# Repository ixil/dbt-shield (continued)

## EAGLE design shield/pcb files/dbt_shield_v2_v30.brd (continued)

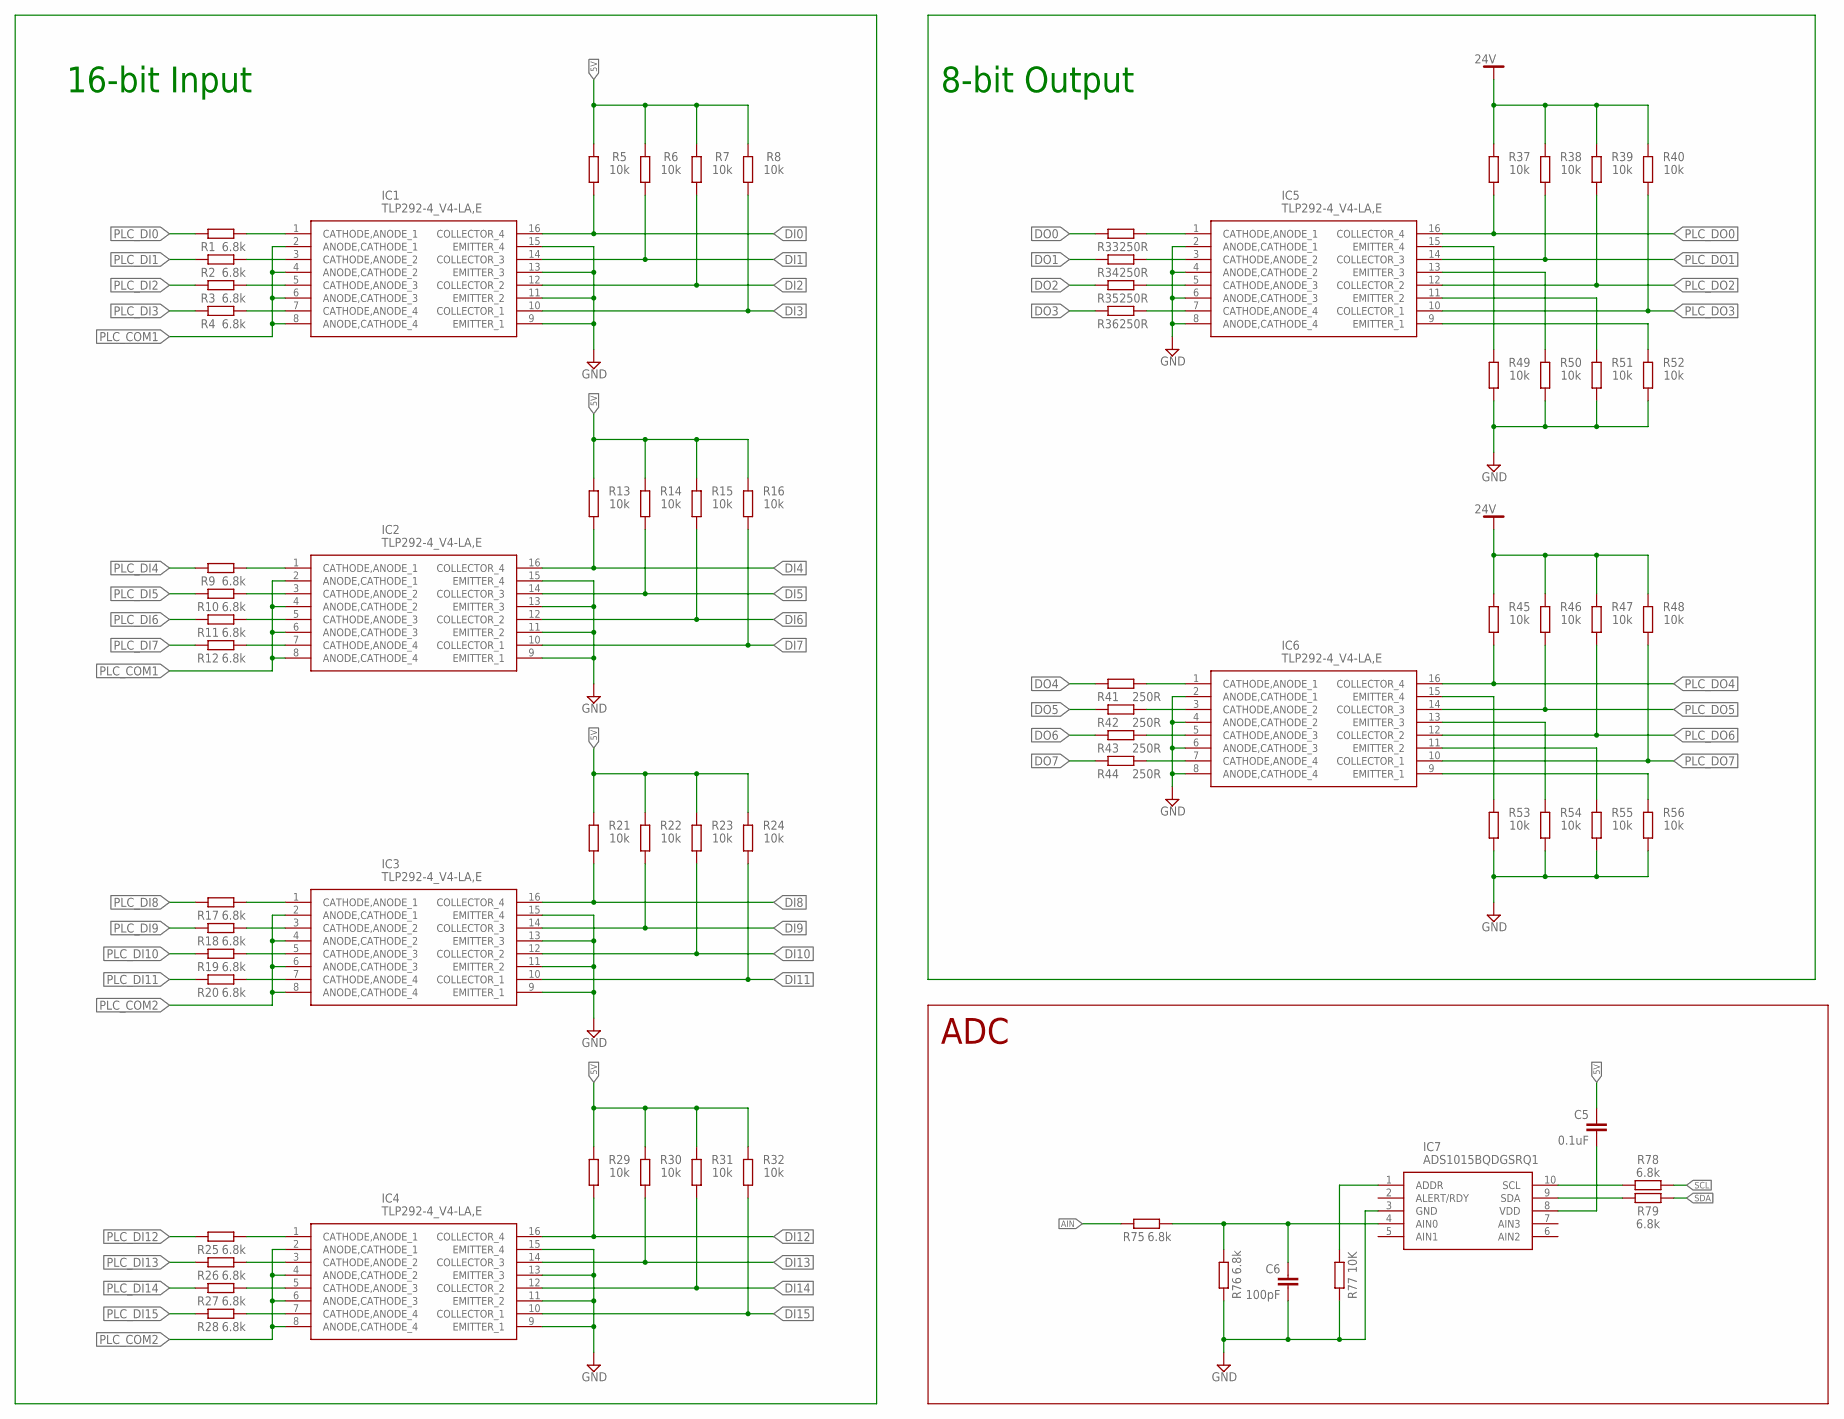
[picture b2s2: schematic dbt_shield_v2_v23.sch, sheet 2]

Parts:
C5: 0.1uF; CAPC3216X135
C6: 100pF; CAPC3216X135
IC1, IC2, IC3, IC4, IC5, IC6: TLP292-4_V4-LA,E; SOIC127P700X230-16N
IC7: ADS1015BQDGSRQ1; SOP50P490X110-10N
R1, R2, R3, R4, R9, R10, R11, R12, R17, R18, R19, R20, R25, R26, R27, R28, R75, R76, R78, R79: 6.8k; RESC3216X70
R5, R6, R7, R8, R13, R14, R15, R16, R21, R22, R23, R24, R29, R30, R31, R32, R37, R38, R39, R40, R45, R46, R47, R48, R49, R50, R51, R52, R53, R54, R55, R56: 10k; RESC3216X70
R33, R34, R35, R36, R41, R42, R43, R44: 250R; RESC3216X70
R77: 10K; RESC3216X70

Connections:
5V: C5.1, R5.2, R6.2, R7.2, R8.2, R13.2, R14.2, R15.2, R16.2, R21.2, R22.2, R23.2, R24.2, R29.2, R30.2, R31.2, R32.2; also elsewhere on the board
24V: R37.2, R38.2, R39.2, R40.2, R45.2, R46.2, R47.2, R48.2; also elsewhere on the board
AIN: R75.1; also elsewhere on the board
DI0: IC1.16 (COLLECTOR_4), R5.1; also elsewhere on the board
DI1: IC1.14 (COLLECTOR_3), R6.1; also elsewhere on the board
DI2: IC1.12 (COLLECTOR_2), R7.1; also elsewhere on the board
DI3: IC1.10 (COLLECTOR_1), R8.1; also elsewhere on the board
DI4: IC2.16 (COLLECTOR_4), R13.1; also elsewhere on the board
DI5: IC2.14 (COLLECTOR_3), R14.1; also elsewhere on the board
DI6: IC2.12 (COLLECTOR_2), R15.1; also elsewhere on the board
DI7: IC2.10 (COLLECTOR_1), R16.1; also elsewhere on the board
DI8: IC3.16 (COLLECTOR_4), R21.1; also elsewhere on the board
DI9: IC3.14 (COLLECTOR_3), R22.1; also elsewhere on the board
DI10: IC3.12 (COLLECTOR_2), R23.1; also elsewhere on the board
DI11: IC3.10 (COLLECTOR_1), R24.1; also elsewhere on the board
DI12: IC4.16 (COLLECTOR_4), R29.1; also elsewhere on the board
DI13: IC4.14 (COLLECTOR_3), R30.1; also elsewhere on the board
DI14: IC4.12 (COLLECTOR_2), R31.1; also elsewhere on the board
DI15: IC4.10 (COLLECTOR_1), R32.1; also elsewhere on the board
DO0: R33.1; also elsewhere on the board
DO1: R34.1; also elsewhere on the board
DO2: R35.1; also elsewhere on the board
DO3: R36.1; also elsewhere on the board
DO4: R41.1; also elsewhere on the board
DO5: R42.1; also elsewhere on the board
DO6: R43.1; also elsewhere on the board
DO7: R44.1; also elsewhere on the board
GND: C6.2, IC1.9 (EMITTER_1), IC1.11 (EMITTER_2), IC1.13 (EMITTER_3), IC1.15 (EMITTER_4), IC2.9 (EMITTER_1), IC2.11 (EMITTER_2), IC2.13 (EMITTER_3), IC2.15 (EMITTER_4), IC3.9 (EMITTER_1), IC3.11 (EMITTER_2), IC3.13 (EMITTER_3), IC3.15 (EMITTER_4), IC4.9 (EMITTER_1), IC4.11 (EMITTER_2), IC4.13 (EMITTER_3), IC4.15 (EMITTER_4), IC5.2 (ANODE,CATHODE_1), IC5.4 (ANODE,CATHODE_2), IC5.6 (ANODE,CATHODE_3), IC5.8 (ANODE,CATHODE_4), IC6.2 (ANODE,CATHODE_1), IC6.4 (ANODE,CATHODE_2), IC6.6 (ANODE,CATHODE_3), IC6.8 (ANODE,CATHODE_4), IC7.3 (GND), R49.1, R50.1, R51.1, R52.1, R53.1, R54.1, R55.1, R56.1, R76.1, R77.1; also elsewhere on the board
unnamed: IC1.1 (CATHODE,ANODE_1), R1.2
unnamed: IC1.3 (CATHODE,ANODE_2), R2.2
unnamed: IC1.5 (CATHODE,ANODE_3), R3.2
unnamed: IC1.7 (CATHODE,ANODE_4), R4.2
unnamed: IC2.1 (CATHODE,ANODE_1), R9.2
unnamed: IC2.3 (CATHODE,ANODE_2), R10.2
unnamed: IC2.5 (CATHODE,ANODE_3), R11.2
unnamed: IC2.7 (CATHODE,ANODE_4), R12.2
unnamed: IC3.1 (CATHODE,ANODE_1), R17.2
unnamed: IC3.3 (CATHODE,ANODE_2), R18.2
unnamed: IC3.5 (CATHODE,ANODE_3), R19.2
unnamed: IC3.7 (CATHODE,ANODE_4), R20.2
unnamed: IC4.1 (CATHODE,ANODE_1), R25.2
unnamed: IC4.3 (CATHODE,ANODE_2), R26.2
unnamed: IC4.5 (CATHODE,ANODE_3), R27.2
unnamed: IC4.7 (CATHODE,ANODE_4), R28.2
unnamed: IC5.1 (CATHODE,ANODE_1), R33.2
unnamed: IC5.3 (CATHODE,ANODE_2), R34.2
unnamed: IC5.5 (CATHODE,ANODE_3), R35.2
unnamed: IC5.7 (CATHODE,ANODE_4), R36.2
unnamed: IC6.1 (CATHODE,ANODE_1), R41.2
unnamed: IC6.3 (CATHODE,ANODE_2), R42.2
unnamed: IC6.5 (CATHODE,ANODE_3), R43.2
unnamed: IC6.7 (CATHODE,ANODE_4), R44.2
unnamed: IC5.15 (EMITTER_4), R49.2
unnamed: IC5.13 (EMITTER_3), R50.2
unnamed: IC5.11 (EMITTER_2), R51.2
unnamed: IC5.9 (EMITTER_1), R52.2
unnamed: IC6.15 (EMITTER_4), R53.2
unnamed: IC6.13 (EMITTER_3), R54.2
unnamed: IC6.11 (EMITTER_2), R55.2
unnamed: IC6.9 (EMITTER_1), R56.2
unnamed: C6.1, IC7.4 (AIN0), R75.2, R76.2
unnamed: IC7.1 (ADDR), R77.2
unnamed: C5.2, IC7.8 (VDD)
unnamed: IC7.9 (SDA), R79.2
unnamed: IC7.10 (SCL), R78.2
PLC_COM1: IC1.2 (ANODE,CATHODE_1), IC1.4 (ANODE,CATHODE_2), IC1.6 (ANODE,CATHODE_3), IC1.8 (ANODE,CATHODE_4), IC2.2 (ANODE,CATHODE_1), IC2.4 (ANODE,CATHODE_2), IC2.6 (ANODE,CATHODE_3), IC2.8 (ANODE,CATHODE_4); also elsewhere on the board
PLC_COM2: IC3.2 (ANODE,CATHODE_1), IC3.4 (ANODE,CATHODE_2), IC3.6 (ANODE,CATHODE_3), IC3.8 (ANODE,CATHODE_4), IC4.2 (ANODE,CATHODE_1), IC4.4 (ANODE,CATHODE_2), IC4.6 (ANODE,CATHODE_3), IC4.8 (ANODE,CATHODE_4); also elsewhere on the board
PLC_DI0: R1.1; also elsewhere on the board
PLC_DI1: R2.1; also elsewhere on the board
PLC_DI2: R3.1; also elsewhere on the board
PLC_DI3: R4.1; also elsewhere on the board
PLC_DI4: R9.1; also elsewhere on the board
PLC_DI5: R10.1; also elsewhere on the board
PLC_DI6: R11.1; also elsewhere on the board
PLC_DI7: R12.1; also elsewhere on the board
PLC_DI8: R17.1; also elsewhere on the board
PLC_DI9: R18.1; also elsewhere on the board
PLC_DI10: R19.1; also elsewhere on the board
PLC_DI11: R20.1; also elsewhere on the board
PLC_DI12: R25.1; also elsewhere on the board
PLC_DI13: R26.1; also elsewhere on the board
PLC_DI14: R27.1; also elsewhere on the board
PLC_DI15: R28.1; also elsewhere on the board
PLC_DO0: IC5.16 (COLLECTOR_4), R37.1; also elsewhere on the board
PLC_DO1: IC5.14 (COLLECTOR_3), R38.1; also elsewhere on the board
PLC_DO2: IC5.12 (COLLECTOR_2), R39.1; also elsewhere on the board
PLC_DO3: IC5.10 (COLLECTOR_1), R40.1; also elsewhere on the board
PLC_DO4: IC6.16 (COLLECTOR_4), R45.1; also elsewhere on the board
PLC_DO5: IC6.14 (COLLECTOR_3), R46.1; also elsewhere on the board
PLC_DO6: IC6.12 (COLLECTOR_2), R47.1; also elsewhere on the board
PLC_DO7: IC6.10 (COLLECTOR_1), R48.1; also elsewhere on the board
SCL: R78.1; also elsewhere on the board
SDA: R79.1; also elsewhere on the board

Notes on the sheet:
16-bit Input
8-bit Output
ADC

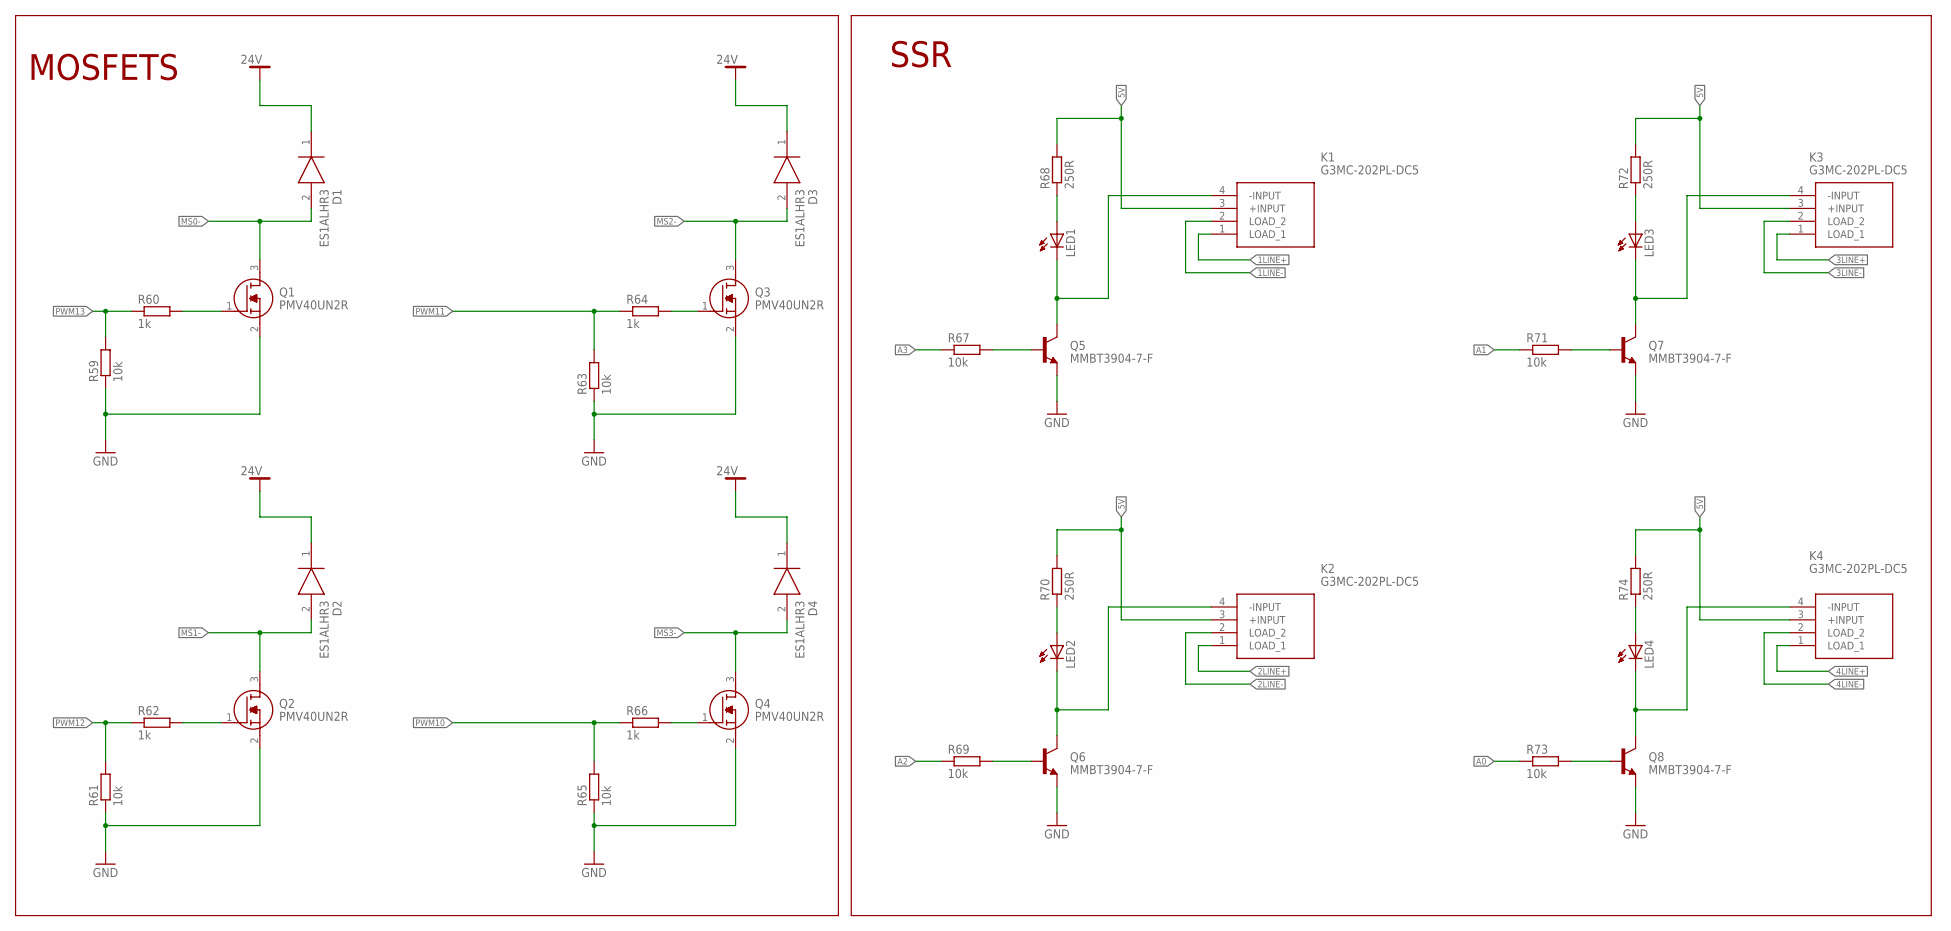
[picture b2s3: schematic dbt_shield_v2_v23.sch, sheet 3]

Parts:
D1, D2, D3, D4: ES1ALHR3; SODFL3618X143N
K1, K2, K3, K4: G3MC-202PL-DC5; G3MC202PLDC5
LED1, LED2, LED3, LED4: LEDCHIPLED_1206; CHIPLED_1206
Q1, Q2, Q3, Q4: PMV40UN2R; SOT95P230X110-3N
Q5, Q6, Q7, Q8: MMBT3904-7-F; SOT95P230X110-3N1
R59, R61, R63, R65, R67, R69, R71, R73: 10k; RESC3216X70
R60, R62, R64, R66: 1k; RESC3216X70
R68, R70, R72, R74: 250R; RESC3216X70

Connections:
1LINE+: K1.1 (LOAD_1); also elsewhere on the board
1LINE-: K1.2 (LOAD_2); also elsewhere on the board
2LINE+: K2.1 (LOAD_1); also elsewhere on the board
2LINE-: K2.2 (LOAD_2); also elsewhere on the board
3LINE+: K3.1 (LOAD_1); also elsewhere on the board
3LINE-: K3.2 (LOAD_2); also elsewhere on the board
4LINE+: K4.1 (LOAD_1); also elsewhere on the board
4LINE-: K4.2 (LOAD_2); also elsewhere on the board
5V: K1.3 (+INPUT), K2.3 (+INPUT), K3.3 (+INPUT), K4.3 (+INPUT), R68.2, R70.2, R72.2, R74.2; also elsewhere on the board
24V: D1.1 (K), D2.1 (K), D3.1 (K), D4.1 (K); also elsewhere on the board
A0: R73.1; also elsewhere on the board
A1: R71.1; also elsewhere on the board
A2: R69.1; also elsewhere on the board
A3: R67.1; also elsewhere on the board
GND: Q1.2 (S), Q2.2 (S), Q3.2 (S), Q4.2 (S), Q5.E, Q6.E, Q7.E, Q8.E, R59.1, R61.1, R63.1, R65.1; also elsewhere on the board
MS0-: D1.2 (A), Q1.3 (D); also elsewhere on the board
MS1-: D2.2 (A), Q2.3 (D); also elsewhere on the board
MS2-: D3.2 (A), Q3.3 (D); also elsewhere on the board
MS3-: D4.2 (A), Q4.3 (D); also elsewhere on the board
unnamed: Q1.1 (G), R60.2
unnamed: Q2.1 (G), R62.2
unnamed: Q3.1 (G), R64.2
unnamed: Q4.1 (G), R66.2
unnamed: LED1.A, R68.1
unnamed: K1.4 (-INPUT), LED1.C, Q5.C
unnamed: Q5.B, R67.2
unnamed: LED2.A, R70.1
unnamed: K2.4 (-INPUT), LED2.C, Q6.C
unnamed: Q6.B, R69.2
unnamed: LED3.A, R72.1
unnamed: K3.4 (-INPUT), LED3.C, Q7.C
unnamed: Q7.B, R71.2
unnamed: LED4.A, R74.1
unnamed: K4.4 (-INPUT), LED4.C, Q8.C
unnamed: Q8.B, R73.2
PWM10: R65.2, R66.1; also elsewhere on the board
PWM11: R63.2, R64.1; also elsewhere on the board
PWM12: R61.2, R62.1; also elsewhere on the board
PWM13: R59.2, R60.1; also elsewhere on the board

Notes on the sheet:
MOSFETS
SSR

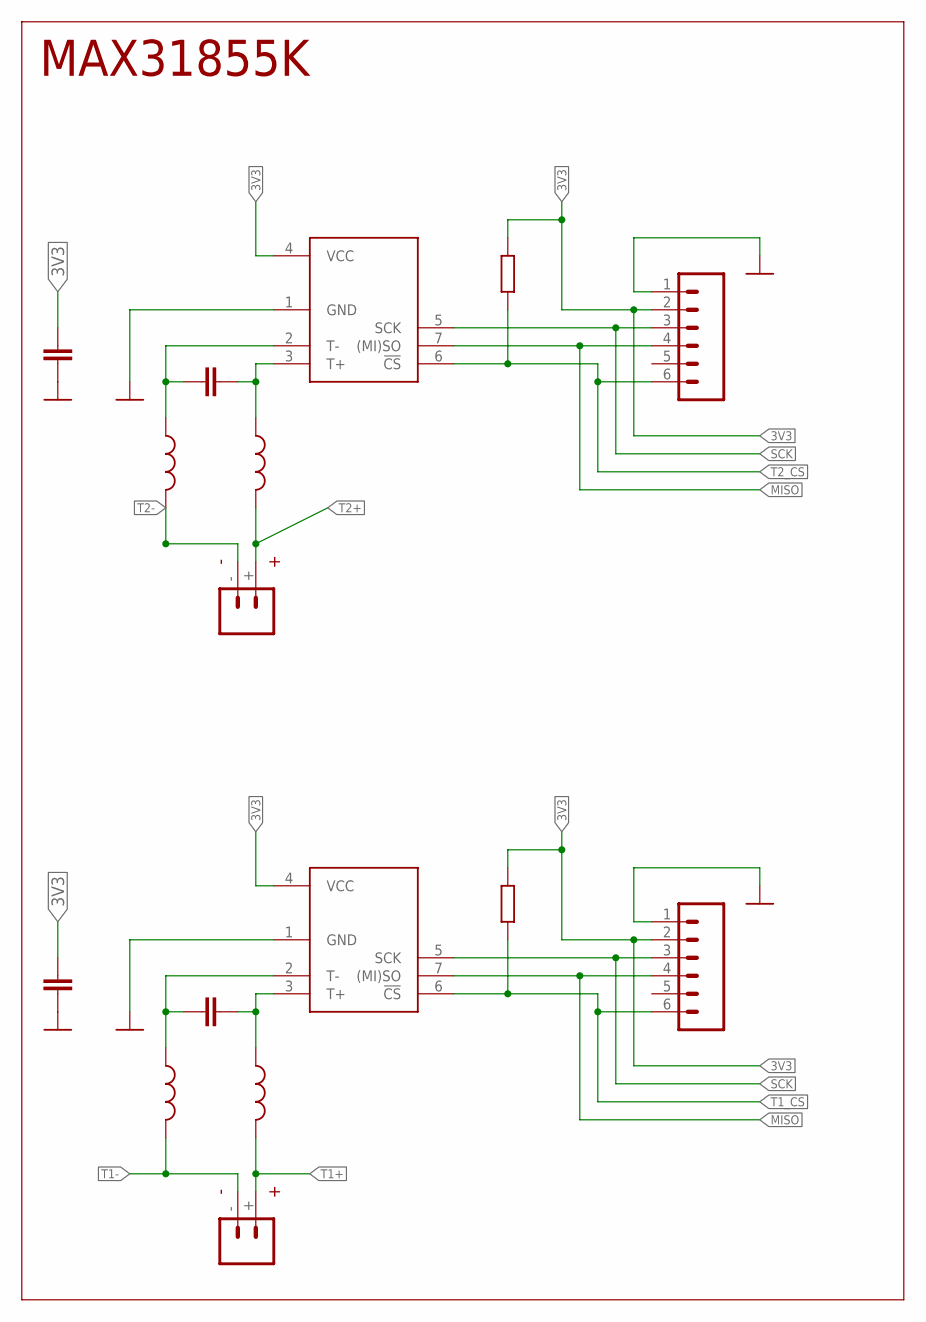
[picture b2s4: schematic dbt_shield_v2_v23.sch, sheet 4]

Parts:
C1, C3: 0.1uF; CAPC3216X135
C2, C4: 10 nF; CAPC3216X135
JP1, JP3: DNP; 1X06
JP2, JP4: PCB_THERMOCOUPLE; PCC-SMP
L1, L2, L3, L4: 470 OHM; INDC3216X190
R57, R58: 10k; RESC3216X70
U2, U3: MAX31855K; SOIC8

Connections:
3V3: C1.1, C3.1, JP1.2, JP3.2, R57.2, R58.2, U2.4 (VCC), U3.4 (VCC); also elsewhere on the board
GND: C1.2, C3.2, JP1.1, JP3.1, U2.1 (GND), U3.1 (GND); also elsewhere on the board
MISO: JP1.4, JP3.4, U2.7 ((MI)SO), U3.7 ((MI)SO); also elsewhere on the board
unnamed: C2.1, L2.1, U2.3 (T+)
unnamed: C4.1, L4.1, U3.3 (T+)
unnamed: C4.2, L3.1, U3.2 (T-)
unnamed: C2.2, L1.1, U2.2 (T-)
SCK: JP1.3, JP3.3, U2.5 (SCK), U3.5 (SCK); also elsewhere on the board
T1+: JP2.+, L2.2; also elsewhere on the board
T1-: JP2.-, L1.2; also elsewhere on the board
T1_CS: JP1.6, R57.1, U2.6 (!CS); also elsewhere on the board
T2+: JP4.+, L4.2; also elsewhere on the board
T2-: JP4.-, L3.2; also elsewhere on the board
T2_CS: JP3.6, R58.1, U3.6 (!CS); also elsewhere on the board

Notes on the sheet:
MAX31855K

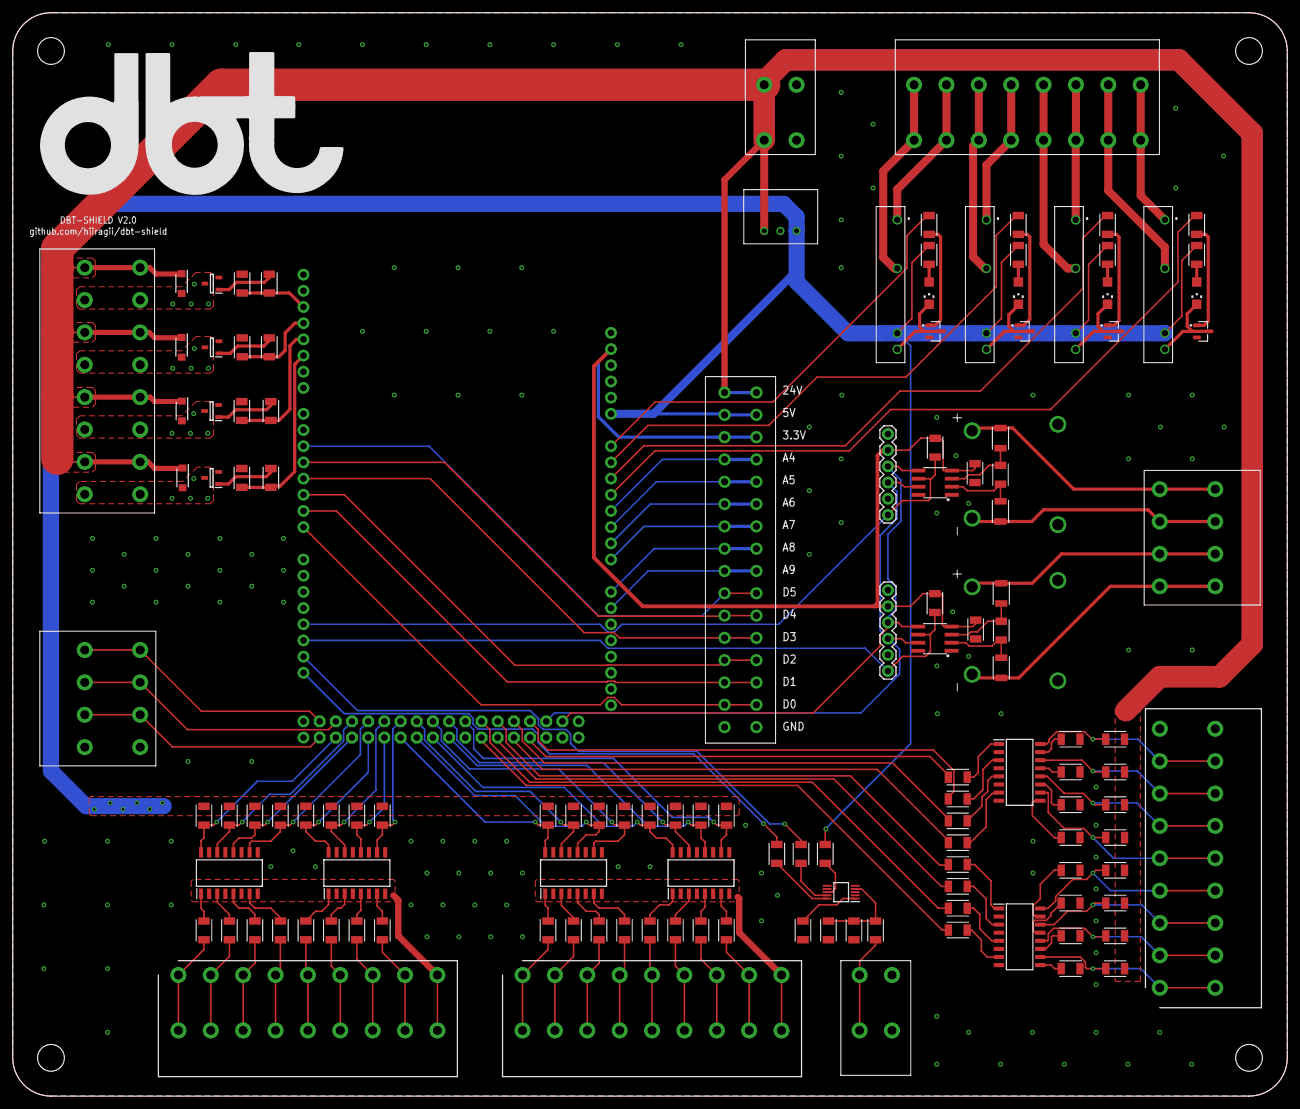
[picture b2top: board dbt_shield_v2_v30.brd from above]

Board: 2 copper layers, 200.0 x 170.0 mm, 134 parts (1 on the bottom side), 157 nets.

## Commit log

2020-09-26 updated pic
2020-09-27 folders
2020-09-27 folder
2020-09-29 arduino
2020-10-06 flows
2020-10-08 ur5aero
2020-10-27 added test
2020-10-27 added pcb files
2020-10-27 pcb files
2020-10-27 new pcb eagle 9 compatible file
2020-11-01 Code
2020-11-01 Add timeout instead of serial print
2020-11-02 Reset timer interrupt flags after sei
